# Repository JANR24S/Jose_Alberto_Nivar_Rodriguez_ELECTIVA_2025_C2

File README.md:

# Jos-Alberto-Nivar-Rodr-guez-20230178-Electiva-C2-2025

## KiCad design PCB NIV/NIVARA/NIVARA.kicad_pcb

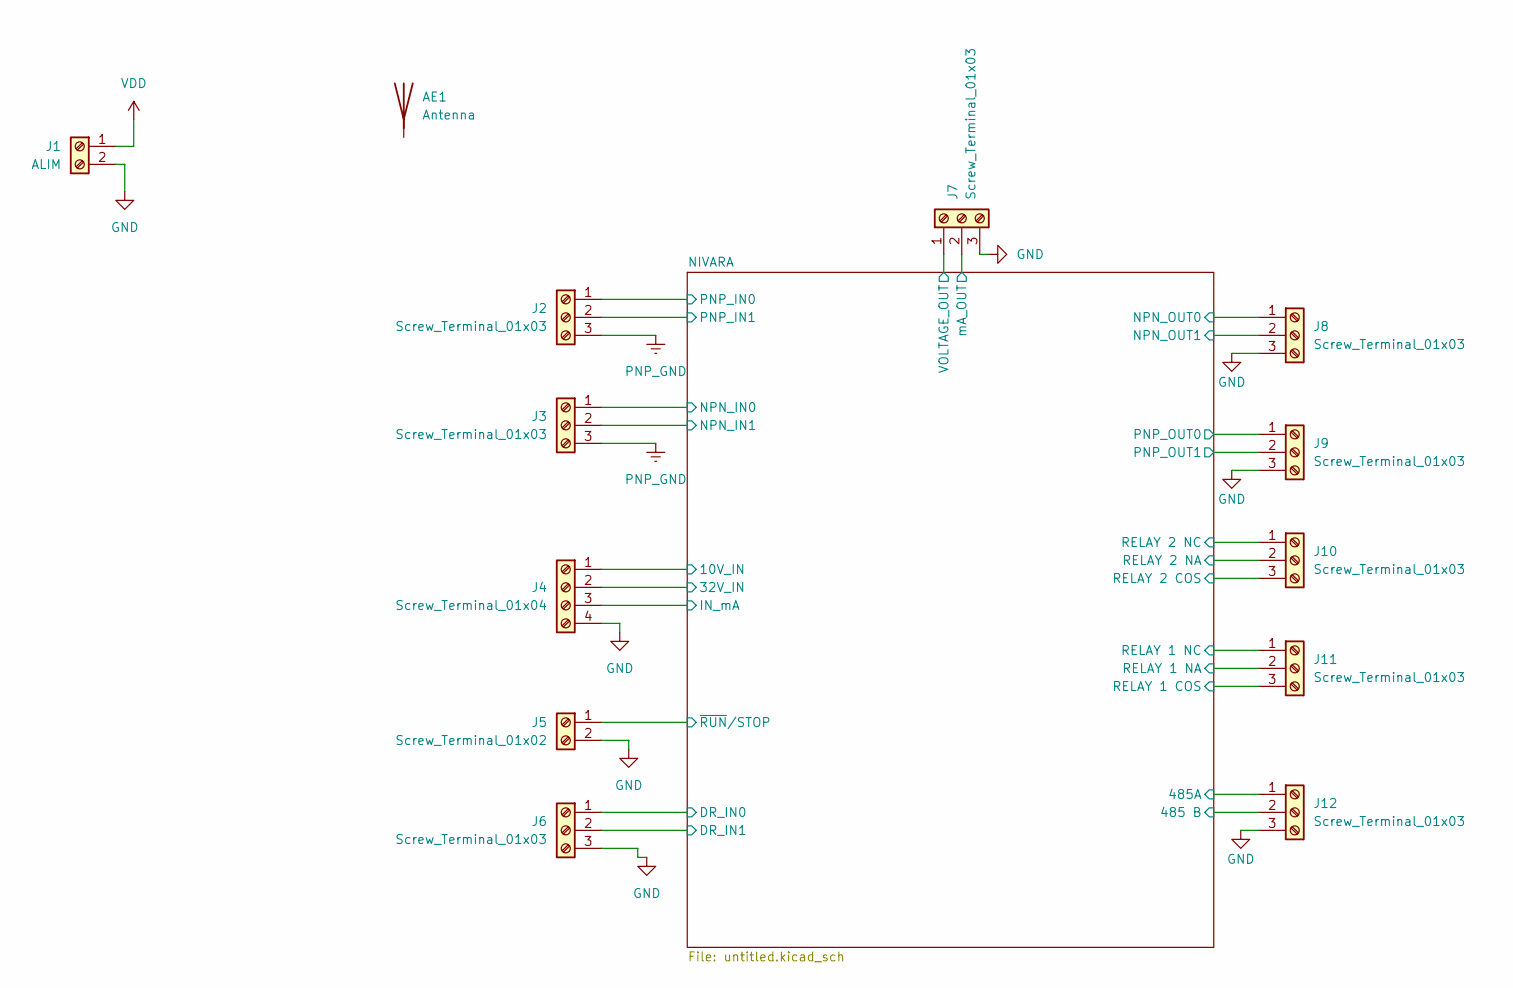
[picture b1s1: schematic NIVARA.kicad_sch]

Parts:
AE1: Antenna
J1: ALIM; TerminalBlock_4Ucon_1x02_P3.50mm_Horizontal
J2, J3, J6, J7, J8, J9, J10, J11, J12: Screw_Terminal_01x03; TerminalBlock_4Ucon_1x03_P3.50mm_Horizontal
J4: Screw_Terminal_01x04; TerminalBlock_4Ucon_1x04_P3.50mm_Horizontal
J5: Screw_Terminal_01x02; TerminalBlock_4Ucon_1x02_P3.50mm_Horizontal

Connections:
/NIVARA/10V_IN: J4.1; also elsewhere on the board
/NIVARA/32V_IN: J4.2; also elsewhere on the board
/NIVARA/485 B: J12.2; also elsewhere on the board
/NIVARA/485A: J12.1; also elsewhere on the board
/NIVARA/DR_IN0: J6.1; also elsewhere on the board
/NIVARA/DR_IN1: J6.2; also elsewhere on the board
/NIVARA/IN_mA: J4.3; also elsewhere on the board
/NIVARA/NPN_IN0: J3.1; also elsewhere on the board
/NIVARA/NPN_IN1: J3.2; also elsewhere on the board
/NIVARA/NPN_OUT0: J8.1; also elsewhere on the board
/NIVARA/NPN_OUT1: J8.2; also elsewhere on the board
/NIVARA/PNP_IN0: J2.1; also elsewhere on the board
/NIVARA/PNP_IN1: J2.2; also elsewhere on the board
/NIVARA/PNP_OUT0: J9.1; also elsewhere on the board
/NIVARA/PNP_OUT1: J9.2; also elsewhere on the board
/NIVARA/RELAY 1 COS: J11.3; also elsewhere on the board
/NIVARA/RELAY 1 NA: J11.2; also elsewhere on the board
/NIVARA/RELAY 1 NC: J11.1; also elsewhere on the board
/NIVARA/RELAY 2 COS: J10.3; also elsewhere on the board
/NIVARA/RELAY 2 NA: J10.2; also elsewhere on the board
/NIVARA/RELAY 2 NC: J10.1; also elsewhere on the board
/NIVARA/VOLTAGE_OUT: J7.1; also elsewhere on the board
/NIVARA/mA_OUT: J7.2; also elsewhere on the board
/NIVARA/~RUN/STOP: J5.1; also elsewhere on the board
GND: J1.2, J4.4, J5.2, J6.3, J7.3, J8.3, J9.3, J12.3; also elsewhere on the board
PNP_GND: J2.3, J3.3; also elsewhere on the board
VDD: J1.1; also elsewhere on the board

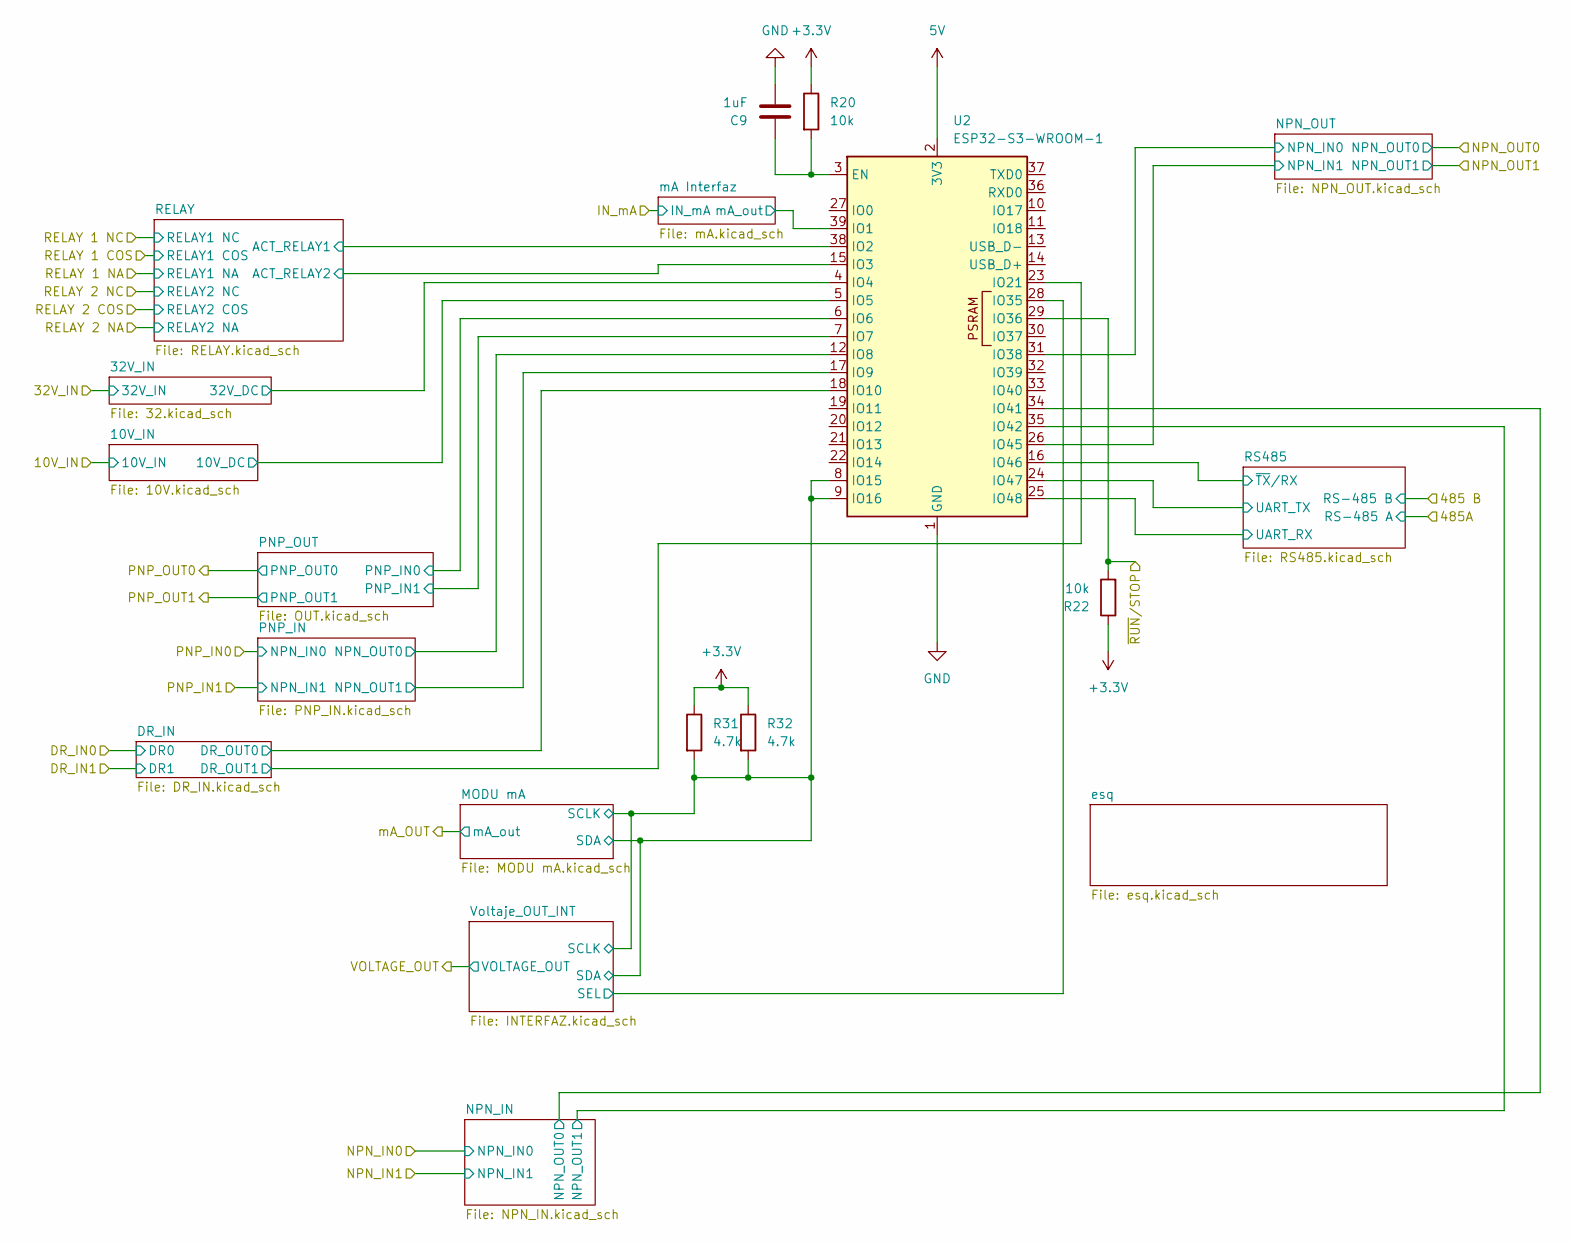
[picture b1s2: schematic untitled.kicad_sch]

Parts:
C9: 1uF; C_0603_1608Metric
R20, R22: 10k; R_0603_1608Metric
R31, R32: 4.7k; R_0603_1608Metric
U2: ESP32-S3-WROOM-1

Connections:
5V: U2.2 (3V3)
+3.3V: R20.1, R22.1, R31.1, R32.1; also elsewhere on the board
/NIVARA/10V_IN/10V_DC: U2.5 (IO5); also elsewhere on the board
/NIVARA/32V_IN/32V_DC: U2.4 (IO4); also elsewhere on the board
/NIVARA/DR_IN/DR_OUT0: U2.18 (IO10); also elsewhere on the board
/NIVARA/DR_IN/DR_OUT1: U2.23 (IO21); also elsewhere on the board
/NIVARA/IN_mA: U2.39 (IO1); also elsewhere on the board
/NIVARA/MODU mA/SCLK: R31.2, R32.2, U2.8 (IO15), U2.9 (IO16); also elsewhere on the board
/NIVARA/NPN_IN/NPN_OUT0: U2.34 (IO41); also elsewhere on the board
/NIVARA/NPN_IN/NPN_OUT1: U2.35 (IO42); also elsewhere on the board
/NIVARA/NPN_OUT/NPN_IN0: U2.31 (IO38); also elsewhere on the board
/NIVARA/NPN_OUT/NPN_IN1: U2.26 (IO45); also elsewhere on the board
/NIVARA/PNP_IN/NPN_OUT0: U2.12 (IO8); also elsewhere on the board
/NIVARA/PNP_IN/NPN_OUT1: U2.17 (IO9); also elsewhere on the board
/NIVARA/PNP_OUT/PNP_IN0: U2.6 (IO6); also elsewhere on the board
/NIVARA/PNP_OUT/PNP_IN1: U2.7 (IO7); also elsewhere on the board
/NIVARA/RELAY/ACT_RELAY1: U2.38 (IO2); also elsewhere on the board
/NIVARA/RELAY/ACT_RELAY2: U2.15 (IO3); also elsewhere on the board
/NIVARA/RS485/UART_RX: U2.25 (IO48); also elsewhere on the board
/NIVARA/RS485/UART_TX: U2.24 (IO47); also elsewhere on the board
/NIVARA/RS485/~TX/RX: U2.16 (IO46); also elsewhere on the board
/NIVARA/Voltaje_OUT_INT/SEL: U2.28 (IO35); also elsewhere on the board
/NIVARA/~RUN/STOP: R22.2, U2.29 (IO36); also elsewhere on the board
GND: C9.2, U2.1 (GND), U2.40 (GND), U2.41 (GND); also elsewhere on the board
unnamed: C9.1, R20.2, U2.3 (EN)

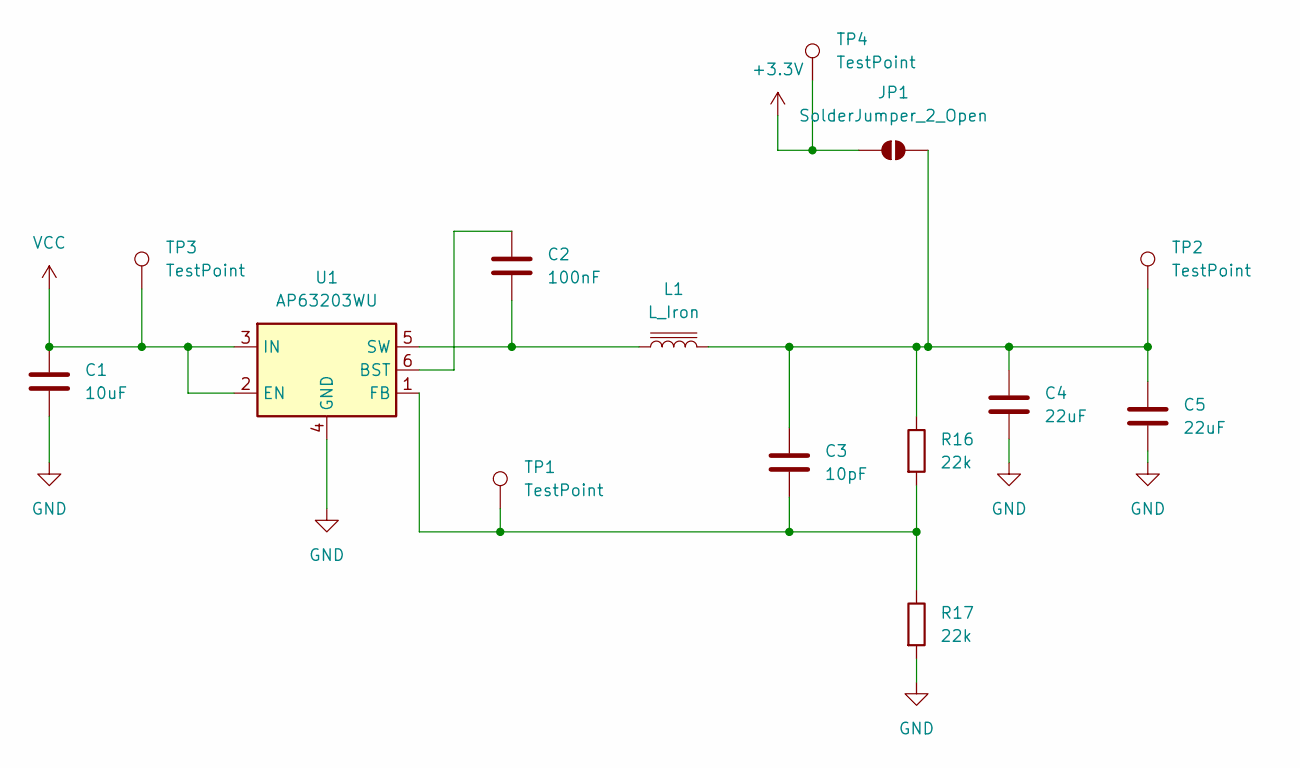
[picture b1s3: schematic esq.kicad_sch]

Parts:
C1: 10uF; C_0603_1608Metric
C2: 100nF; C_0603_1608Metric
C3: 10pF; C_0603_1608Metric
C4, C5: 22uF; C_0603_1608Metric
JP1: SolderJumper_2_Open; SolderJumper-2_P1.3mm_Open_Pad1.0x1.5mm
L1: L_Iron; L_Wurth_WE-LQSH-2512
R16, R17: 22k; R_0603_1608Metric
TP1, TP2, TP3, TP4: TestPoint; Pin_D1.0mm_L10.0mm
U1: AP63203WU; TSOT-23-6

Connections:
+3.3V: JP1.1 (A), TP4.1; also elsewhere on the board
GND: C1.2, C4.1, C5.1, R17.1, U1.4 (GND); also elsewhere on the board
unnamed: C3.2, C4.2, C5.2, JP1.2 (B), L1.2, R16.2, TP2.1
unnamed: C2.1, U1.6 (BST)
unnamed: C3.1, R16.1, R17.2, TP1.1, U1.1 (FB)
unnamed: C2.2, L1.1, U1.5 (SW)
VCC: C1.1, TP3.1, U1.2 (EN), U1.3 (IN); also elsewhere on the board

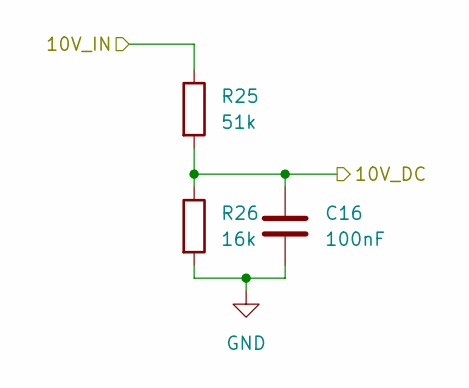
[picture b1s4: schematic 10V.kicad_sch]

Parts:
C16: 100nF; C_0603_1608Metric
R25: 51k; R_0603_1608Metric
R26: 16k; R_0603_1608Metric

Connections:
/NIVARA/10V_IN: R25.1; also elsewhere on the board
/NIVARA/10V_IN/10V_DC: C16.1, R25.2, R26.1; also elsewhere on the board
GND: C16.2, R26.2; also elsewhere on the board

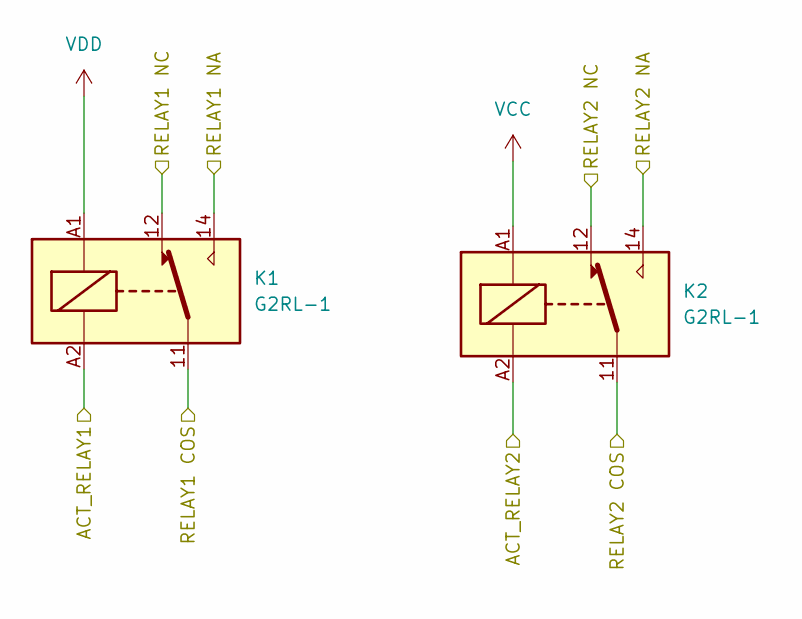
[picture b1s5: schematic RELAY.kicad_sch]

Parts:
K1, K2: G2RL-1; Relay_SPDT_Omron_G2RL-1

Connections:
/NIVARA/RELAY 1 COS: K1.11; also elsewhere on the board
/NIVARA/RELAY 1 NA: K1.14; also elsewhere on the board
/NIVARA/RELAY 1 NC: K1.12; also elsewhere on the board
/NIVARA/RELAY 2 COS: K2.11; also elsewhere on the board
/NIVARA/RELAY 2 NA: K2.14; also elsewhere on the board
/NIVARA/RELAY 2 NC: K2.12; also elsewhere on the board
/NIVARA/RELAY/ACT_RELAY1: K1.A2; also elsewhere on the board
/NIVARA/RELAY/ACT_RELAY2: K2.A2; also elsewhere on the board
VCC: K2.A1; also elsewhere on the board
VDD: K1.A1; also elsewhere on the board

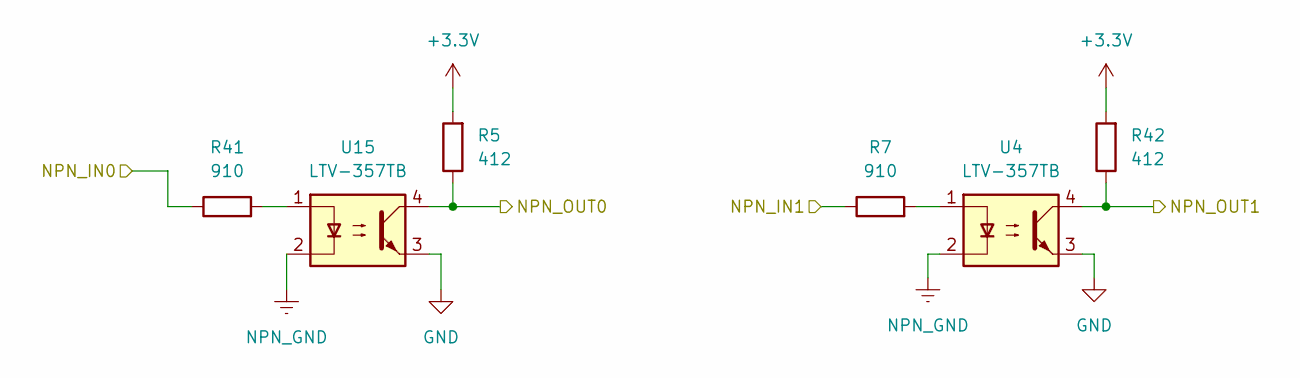
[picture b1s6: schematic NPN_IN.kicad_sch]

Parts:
R5, R42: 412; R_0603_1608Metric
R7, R41: 910; R_0603_1608Metric; LCSC# C114670
U4, U15: LTV-357TB; SO-4_4.4x3.6mm_P2.54mm

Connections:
+3.3V: R5.2, R42.2; also elsewhere on the board
/NIVARA/NPN_IN0: R41.1; also elsewhere on the board
/NIVARA/NPN_IN1: R7.1; also elsewhere on the board
/NIVARA/NPN_IN/NPN_OUT0: R5.1, U15.4; also elsewhere on the board
/NIVARA/NPN_IN/NPN_OUT1: R42.1, U4.4; also elsewhere on the board
GND: U4.3, U15.3; also elsewhere on the board
NPN_GND: U4.2, U15.2
unnamed: R7.2, U4.1
unnamed: R41.2, U15.1

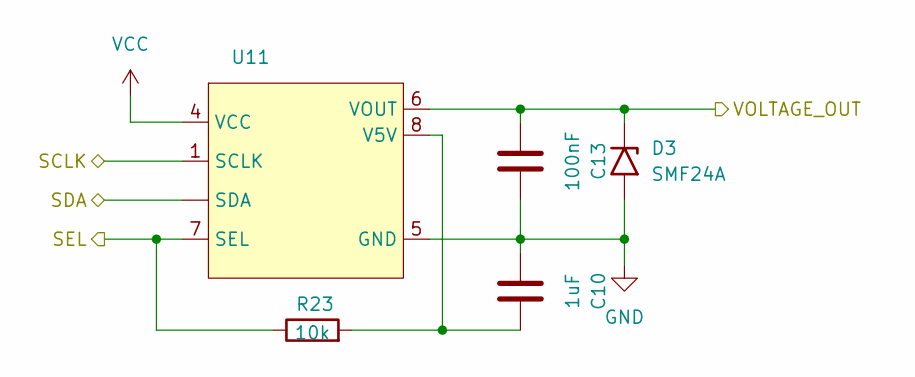
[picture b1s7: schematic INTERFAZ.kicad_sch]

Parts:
C10: 1uF; C_0603_1608Metric
C13: 100nF; C_0603_1608Metric
D3: SMF24A; D_SMF; LCSC# C7495269
R23: 10k; R_0603_1608Metric
U11: SOP-8_3.76x4.96mm_P1.27mm

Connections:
/NIVARA/MODU mA/SCLK: U11.1 (SCLK); also elsewhere on the board
/NIVARA/VOLTAGE_OUT: C13.2, D3.1 (A1), U11.6 (VOUT); also elsewhere on the board
/NIVARA/Voltaje_OUT_INT/SEL: R23.1, U11.7 (SEL); also elsewhere on the board
GND: C10.2, C13.1, D3.2 (A2), U11.5 (GND); also elsewhere on the board
unnamed: C10.1, R23.2, U11.8 (V5V)
VCC: U11.4 (VCC); also elsewhere on the board

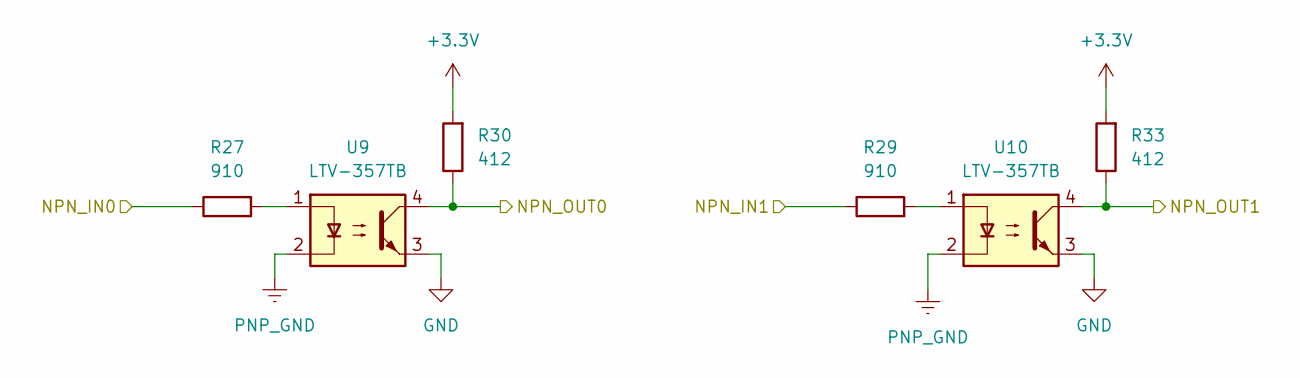
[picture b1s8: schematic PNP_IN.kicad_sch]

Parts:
R27, R29: 910; R_0603_1608Metric; LCSC# C114670
R30, R33: 412; R_0603_1608Metric
U9, U10: LTV-357TB; SO-4_4.4x3.6mm_P2.54mm

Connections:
+3.3V: R30.2, R33.2; also elsewhere on the board
/NIVARA/PNP_IN0: R27.1; also elsewhere on the board
/NIVARA/PNP_IN1: R29.1; also elsewhere on the board
/NIVARA/PNP_IN/NPN_OUT0: R30.1, U9.4; also elsewhere on the board
/NIVARA/PNP_IN/NPN_OUT1: R33.1, U10.4; also elsewhere on the board
GND: U9.3, U10.3; also elsewhere on the board
unnamed: R27.2, U9.1
unnamed: R29.2, U10.1
PNP_GND: U9.2, U10.2; also elsewhere on the board

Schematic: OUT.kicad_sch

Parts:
R34, R35: 100; R_0603_1608Metric
U13, U14: SO-4_4.4x4.3mm_P2.54mm

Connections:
/NIVARA/PNP_OUT0: U13.4; also elsewhere on the board
/NIVARA/PNP_OUT1: U14.4; also elsewhere on the board
/NIVARA/PNP_OUT/PNP_IN0: R34.1; also elsewhere on the board
/NIVARA/PNP_OUT/PNP_IN1: R35.1; also elsewhere on the board
GND: U13.2, U14.2; also elsewhere on the board
unnamed: R34.2, U13.1
unnamed: R35.2, U14.1
VCC: U13.3, U14.3; also elsewhere on the board

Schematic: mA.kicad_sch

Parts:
C15: 100nF; C_0603_1608Metric
R28: 120; R_0603_1608Metric

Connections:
/NIVARA/IN_mA: C15.1, R28.1; also elsewhere on the board
GND: C15.2, R28.2; also elsewhere on the board

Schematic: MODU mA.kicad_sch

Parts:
C6: 220pF; C_0402_1005Metric
C7: 1uF; C_0402_1005Metric
C11: 1uF; C_0603_1608Metric
C12: 0.1uF; C_0603_1608Metric
D4: 1N4007; D_0201_0603Metric
D6, D7: SMF24A; D_0201_0603Metric; LCSC# C7495269
JP2, JP3, JP4: SolderJumper_2_Open; SolderJumper-2_P1.3mm_Open_Pad1.0x1.5mm
Q1: AO3401A; SOT-23
R9, R10, R11: 10K; R_0603_1608Metric
R14: 2.5k; R_0603_1608Metric
R18: 100k; R_0603_1608Metric
R19: 15; R_0603_1608Metric
U3: SSOP-10-1EP_3.9x4.9mm_P1mm_EP2.1x3.3mm

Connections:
/NIVARA/MODU mA/SCLK: U3.1 (SCLK), U3.2 (SDA); also elsewhere on the board
/NIVARA/mA_OUT: D4.1 (K); also elsewhere on the board
GND: C6.2, C7.2, C11.2, C12.2, D6.2 (A2), JP2.1 (A), JP3.1 (A), JP4.1 (A), R14.2, R18.2, U3.6 (GND); also elsewhere on the board
unnamed: D4.2 (A), R19.2
unnamed: C12.1, D6.1 (A1), Q1.3 (D), R19.1
unnamed: C11.1, D7.2 (A2), Q1.1 (G), R18.1
unnamed: JP2.2 (B), JP3.2 (B), R10.2, R11.2, U3.4 (A1), U3.9 (A2)
unnamed: JP4.2 (B), R9.2, U3.3 (A0)
unnamed: C6.1, R14.1, U3.7 (SET)
unnamed: C7.1, R9.1, R10.1, R11.1, U3.10 (V5V)
VCC: D7.1 (A1); also elsewhere on the board
VDD: U3.5 (VCC); also elsewhere on the board
i_out: Q1.2 (S), U3.8 (IOUT)

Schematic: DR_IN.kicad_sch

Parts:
R36, R38: 910; R_0603_1608Metric; LCSC# C114670
R37, R39: 412; R_0603_1608Metric
U7, U8: LTV-357TB; SO-4_4.4x3.6mm_P2.54mm

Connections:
+3.3V: R37.2, R39.2; also elsewhere on the board
/NIVARA/DR_IN0: U7.2; also elsewhere on the board
/NIVARA/DR_IN1: U8.2; also elsewhere on the board
/NIVARA/DR_IN/DR_OUT0: R37.1, U7.4; also elsewhere on the board
/NIVARA/DR_IN/DR_OUT1: R39.1, U8.4; also elsewhere on the board
GND: U7.3, U8.3; also elsewhere on the board
unnamed: R36.2, U7.1
unnamed: R38.2, U8.1
VCC: R36.1, R38.1; also elsewhere on the board

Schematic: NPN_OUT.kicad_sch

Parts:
R4: 100; R_0201_0603Metric
R40: 100; R_0603_1608Metric
U6, U12: SO-4_4.4x4.3mm_P2.54mm

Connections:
/NIVARA/NPN_OUT0: U6.3; also elsewhere on the board
/NIVARA/NPN_OUT1: U12.3; also elsewhere on the board
/NIVARA/NPN_OUT/NPN_IN0: R4.1; also elsewhere on the board
/NIVARA/NPN_OUT/NPN_IN1: R40.1; also elsewhere on the board
GND: U6.2, U6.4, U12.2, U12.4; also elsewhere on the board
unnamed: R4.2, U6.1
unnamed: R40.2, U12.1

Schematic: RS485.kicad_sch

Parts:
C8: 100nF; C_0201_0603Metric
R12, R13, R15: 10K; R_0603_1608Metric
U5: SP3485EN; SOIC-8_3.9x4.9mm_P1.27mm

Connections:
/NIVARA/485 B: R13.2, R15.1, U5.7 (B); also elsewhere on the board
/NIVARA/485A: R12.2, R13.1, U5.6 (A); also elsewhere on the board
/NIVARA/RS485/UART_RX: U5.1 (RO); also elsewhere on the board
/NIVARA/RS485/UART_TX: U5.4 (DI); also elsewhere on the board
/NIVARA/RS485/~TX/RX: U5.2 (~RE), U5.3 (DE); also elsewhere on the board
GND: C8.2, R15.2, U5.5 (GND); also elsewhere on the board
VDD: C8.1, R12.1, U5.8 (VCC); also elsewhere on the board

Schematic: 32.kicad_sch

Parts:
C14: 100nF; C_0603_1608Metric
R21: 160k; R_0603_1608Metric
R24: 13k; R_0603_1608Metric

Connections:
/NIVARA/32V_IN: R21.1; also elsewhere on the board
/NIVARA/32V_IN/32V_DC: C14.1, R21.2, R24.1; also elsewhere on the board
GND: C14.2, R24.2; also elsewhere on the board

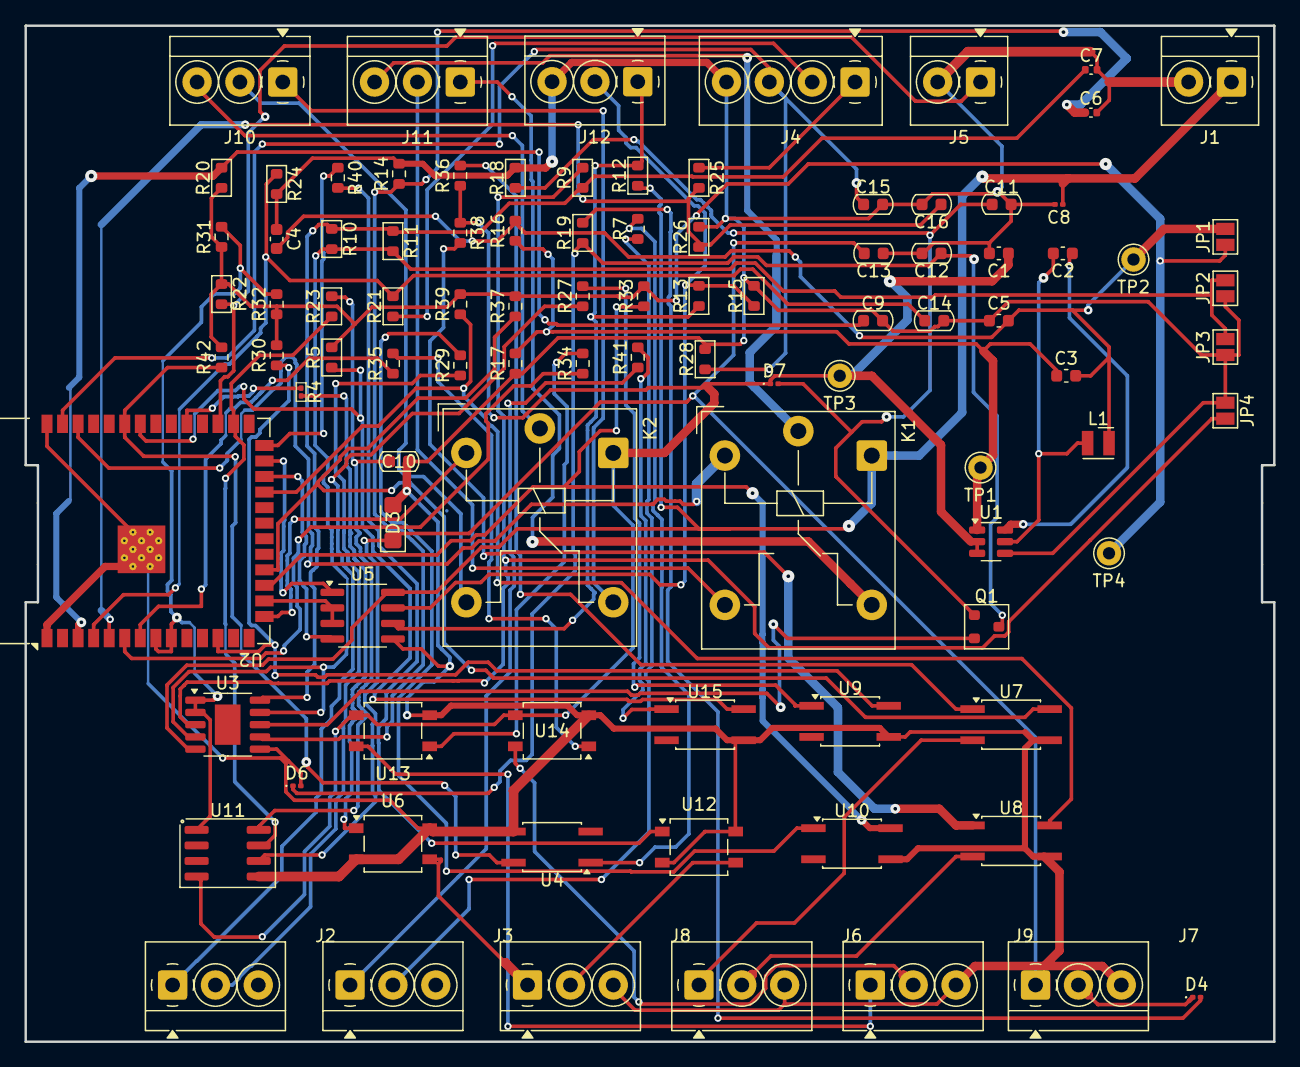
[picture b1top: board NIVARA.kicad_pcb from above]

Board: 4 copper layers, 102.0 x 83.0 mm, 96 parts (0 on the bottom side), 73 nets.

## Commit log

2025-08-15 Create MBSE
